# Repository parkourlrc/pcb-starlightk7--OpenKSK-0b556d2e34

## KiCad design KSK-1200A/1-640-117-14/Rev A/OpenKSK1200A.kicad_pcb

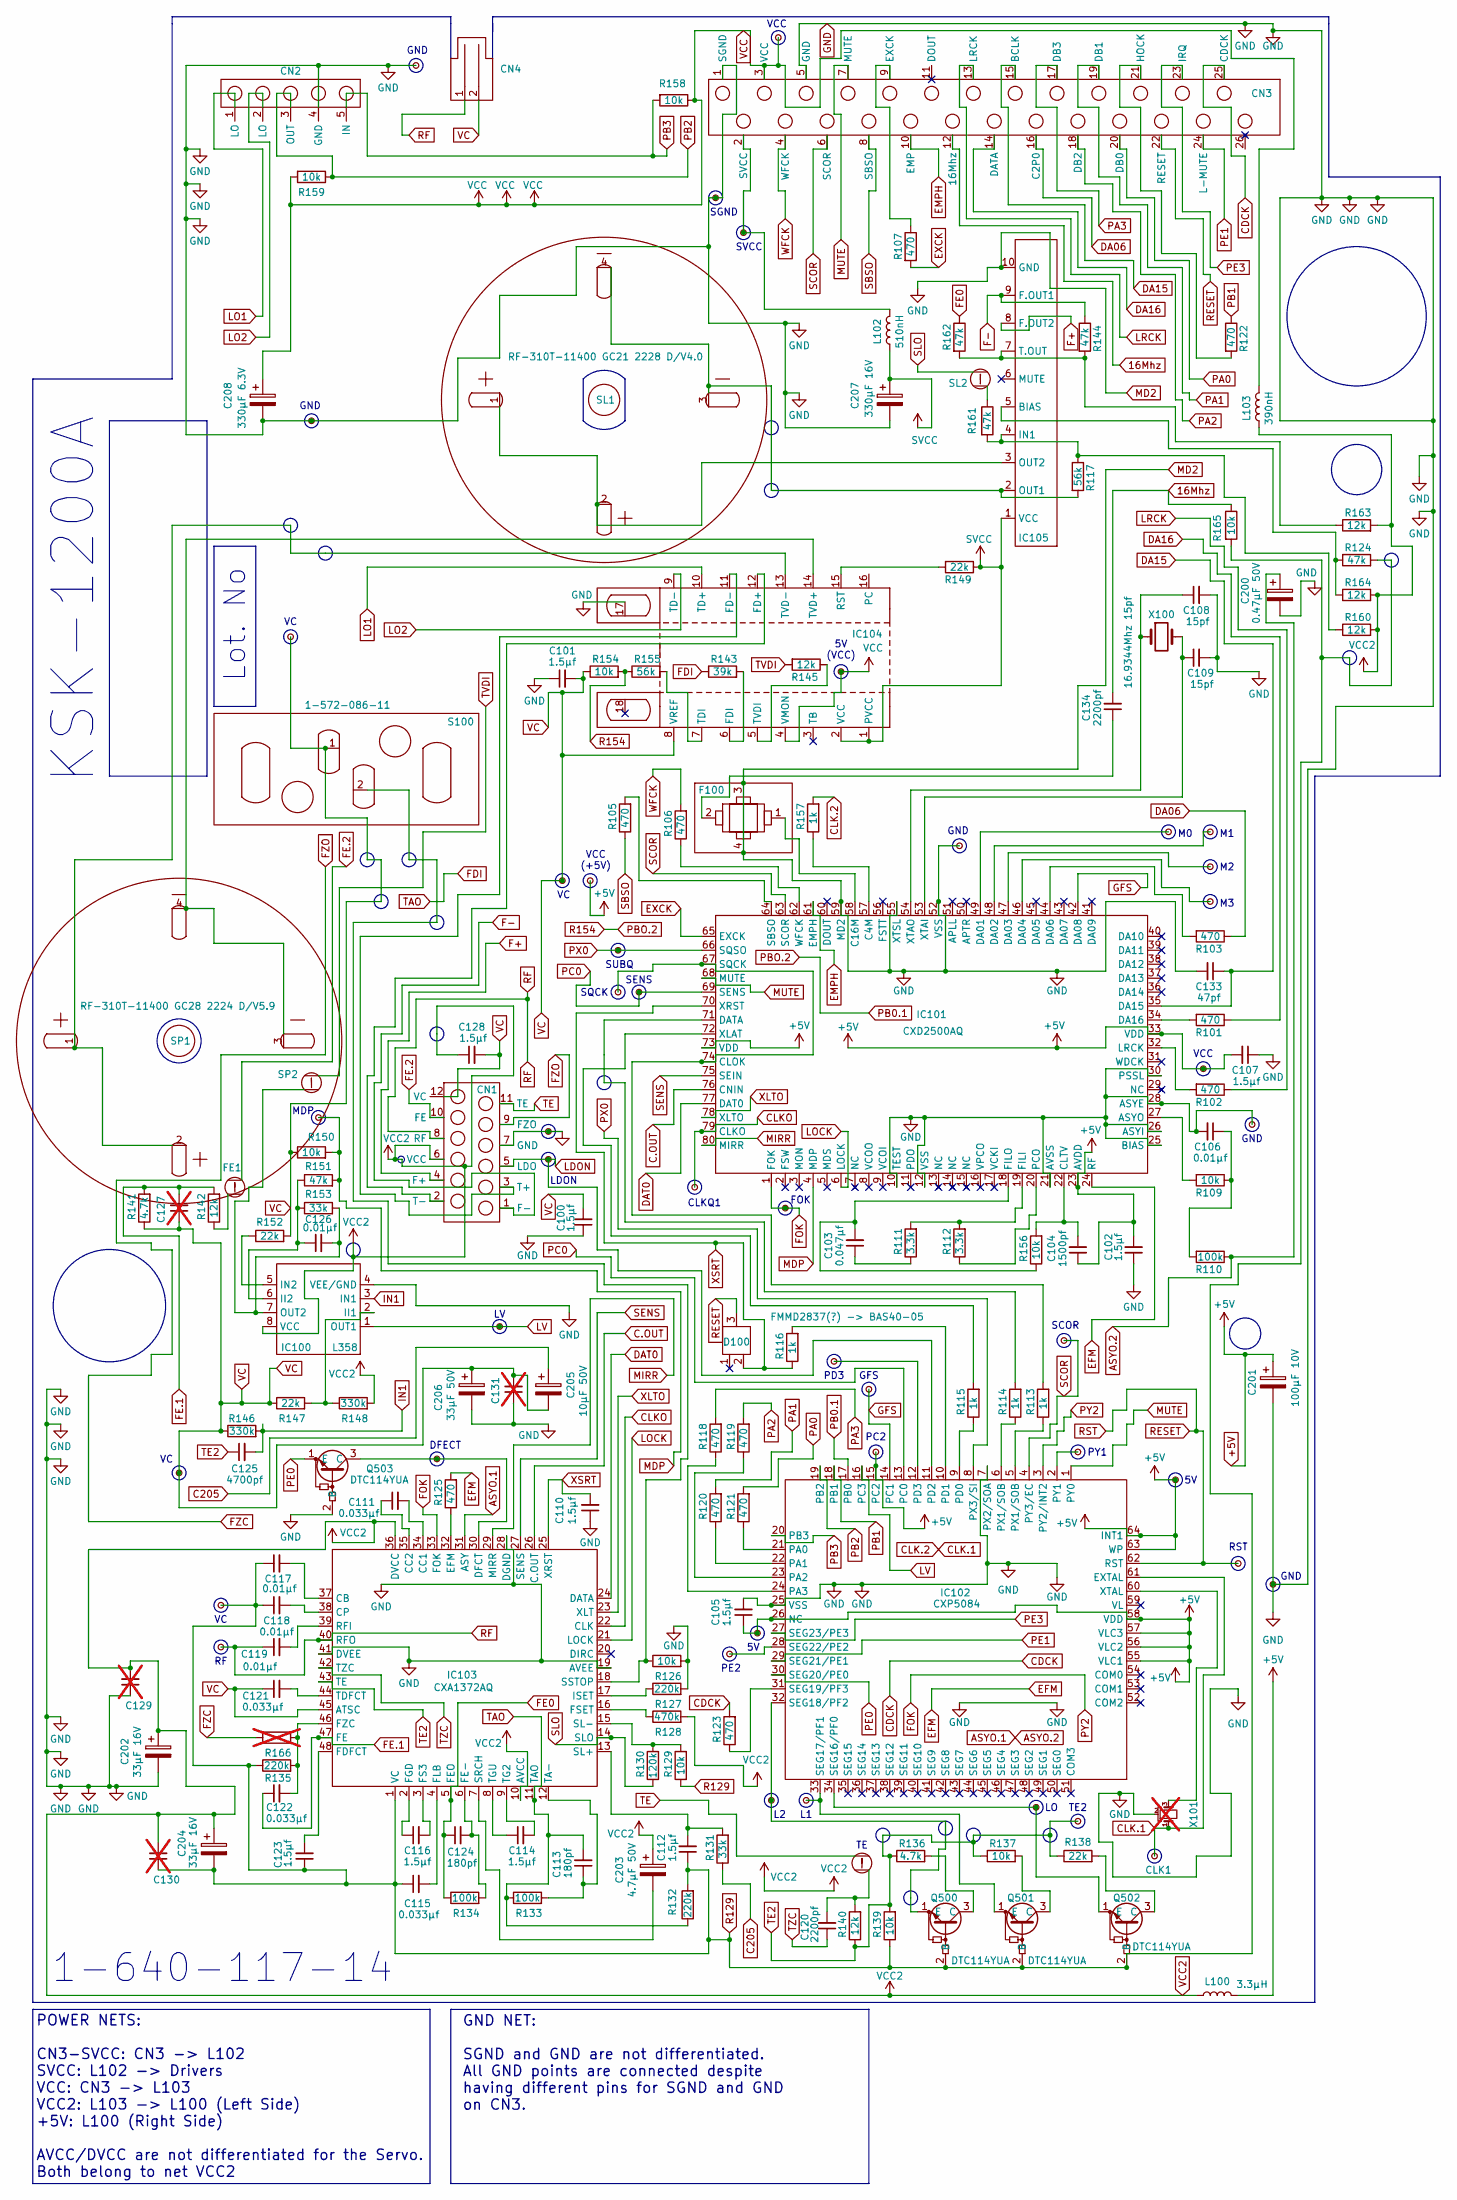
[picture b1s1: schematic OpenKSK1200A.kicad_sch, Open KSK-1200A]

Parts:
5V1, 5V2, 5V3: TestPoint_Small; TestPoint_Pad_D1.0mm
5V4: TestPoint_Small; TestPoint_Pad_D2.0mm
C100, C101, C102, C105, C107, C110, C112, C114, C116, C123, C128: 1.5µf; C_0805_2012Metric
C103: 0.047µf; C_0805_2012Metric
C104: 1500pf; C_0805_2012Metric
C106, C117, C118, C119, C126: 0.01µf; C_0805_2012Metric
C108, C109: 15pf; C_0805_2012Metric
C111, C115, C121, C122: 0.033µf; C_0805_2012Metric
C113, C124: 180pf; C_0805_2012Metric
C120, C134: 2200pf; C_0805_2012Metric
C125: 4700pf; C_0805_2012Metric
C127, C131: C_0805_2012Metric; not fitted
C129, C130: C_Small; C_0805_2012Metric; not fitted
C133: 47pf; C_0805_2012Metric
C200: 0.47µF 50V; THT Cap 0.5_0.5
C201: 100µF 10V; THT Cap 0.5_0.5
C202, C204: 33µF 16V; THT Cap 0.5_0.5
C203: 4.7µF 50V; THT Cap 0.5_0.5
C205: 10µF 50V; THT Cap 0.5_0.5
C206: 33µF 50V; THT Cap 0.5_0.5
C207: 330µF 16V; THT Cap 0.5_0.5
C208: 330µF 6.3V; THT Cap 0.5_0.5
CLK1: TestPoint_Small; TestPoint_Pad_D1.0mm
CLKQ1: TestPoint_Small; TestPoint_Pad_D1.0mm
CN1: CN1
CN2: CN2
CN3: CN3
CN4: CN4
D100: FMMD2837(?) -> BAS40-05; SOT-23_Handsoldering
DFECT1: TestPoint_Small; TestPoint_Pad_D1.0mm
F100: 350nH (L/R); F100
FE1: Jumper
FOK1: TestPoint_Small; TestPoint_Pad_D1.0mm
GFS1: TestPoint_Small; TestPoint_Pad_D2.0mm
GND1, GND2, GND4, GND5, GND6: TestPoint_Small; TestPoint_Pad_D2.0mm
GND3: TestPoint_Small; TestPoint_Pad_D1.0mm
IC100: L358; LM358
IC101: CXD2500AQ
IC102: CXP5084
IC103: CXA1372AQ; CXA1372Q
IC104: AN8377N
IC105: BA6294
L1, L2: TestPoint_Small; TestPoint_Pad_D1.0mm
L100: 3.3μH; L_1206_3216Metric
L102: 510nH; L_1806_4516Metric_Pad1.45x1.90mm_HandSolder
L103: 390nH; L_1206_3216Metric
LDON1: TestPoint_Small; TestPoint_Pad_D2.0mm
LO1: TestPoint_Small; TestPoint_Pad_D2.0mm
LV1: TestPoint_Small; TestPoint_Pad_D2.0mm
M0, M1, M2, M3: TestPoint_Small; TestPoint_Pad_D2.0mm
MDP1: TestPoint_Small; TestPoint_Pad_D2.0mm
PC2: TestPoint_Small; TestPoint_Pad_D1.0mm
PD3: TestPoint_Small; TestPoint_Pad_D2.0mm
PE2: TestPoint_Small; TestPoint_Pad_D2.0mm
PY1: TestPoint_Small; TestPoint_Pad_D2.0mm
Q500, Q501, Q502, Q503: DTC114YUA; SOT-323_SC-70
R101, R102, R103, R105, R106, R107, R118, R119, R120, R121, R122, R123, R125: 470; R_0805_2012Metric
R109, R126, R129, R137, R139, R150, R154, R156, R158, R159, R165: 10k; R_0805_2012Metric
R110, R133, R134: 100k; R_0805_2012Metric
R111, R112: 3.3k; R_0805_2012Metric
R113, R114, R115, R116, R157: 1k; R_0805_2012Metric
R117, R155: 56k; R_0805_2012Metric
R124, R144, R151, R161, R162: 47k; R_0805_2012Metric
R127, R132, R135: 220k; R_0805_2012Metric
R128: 470k; R_0805_2012Metric
R130: 120k; R_0805_2012Metric
R131, R153: 33k; R_0805_2012Metric
R136, R141: 4.7k; R_0805_2012Metric
R138, R147, R149, R152: 22k; R_0805_2012Metric
R140, R142, R145, R160, R163, R164: 12k; R_0805_2012Metric
R143: 39k; R_0805_2012Metric
R146, R148: 330k; R_0805_2012Metric
R166: R_0805_2012Metric; not fitted
RF1: TestPoint_Pad_D2.0mm
RST1: TestPoint_Small; TestPoint_Pad_D2.0mm
S100: 1-572-086-11; LimitSwitch
SCOR1: TestPoint_Small; TestPoint_Pad_D2.0mm
SENS1: TestPoint_Small; TestPoint_Pad_D1.0mm
SGND1: TestPoint_Small; TestPoint_Pad_D2.0mm
SL1: RF-310T-11400 GC21 2228 D/V4.0; SL1
SL2: Jumper
SP1: RF-310T-11400 GC28 2224 D/V5.9; SP1
SP2: Jumper
SQCK1: TestPoint_Small; TestPoint_Pad_D1.0mm
SUBG1: TestPoint_Small; TestPoint_Pad_D1.0mm
SVCC1: TestPoint_Small; TestPoint_Pad_D2.0mm
TE1: Jumper
TE2: TestPoint_Small; TestPoint_Pad_D2.0mm
VC1, VC2: TestPoint_Pad_D1.0mm
VC3, VC4: TestPoint_Small; TestPoint_Pad_D2.0mm
VCC2: TestPoint_Small; TestPoint_Pad_D2.0mm
VCC3: TestPoint_Small; TestPoint_Pad_D1.0mm
X100: 16.9344Mhz 15pf; Crystal_HC18-U_Vertical
X101: Crystal_HC49-U-3Pin_Vertical; not fitted

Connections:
16Mhz: C134.2, CN3.12 (16Mhz), R165.1
+5V: 5V1.1, 5V2.1, 5V4.1, C102.2, C104.1, C105.1, C107.2, C201.1, IC101.23 (AVDD), IC101.33 (VDD), IC101.73 (VDD), IC102.15 (PC2), IC102.26 (NC), IC102.55 (VLC1), IC102.56 (VLC2), IC102.57 (VLC3), IC102.58 (VDD), IC102.63 (WP), IC102.64 (INT1), L100.2, PC2.1, VCC3.1
ASYO.1: C200.1, IC103.31 (ASY), R110.1
C205: C205.1, R131.1
C.OUT: IC101.76 (CNIN), IC103.26 (C.OUT)
CDCK: CN3.25 (CDCK), R123.2
CLK.1: CLK1.1, IC102.61 (EXTAL), R157.2, X101.1
CLKO: CLKQ1.1, IC101.79 (CLKO), IC103.22 (CLK)
DA06: CN3.16 (C2P0), R103.1
DA15: C133.1, CN3.15 (BCLK), IC101.35 (DA15)
DA16: CN3.14 (DATA), R101.1
DAT0: IC101.77 (DAT0), IC103.24 (DATA)
EFM: IC101.24 (RF), R125.2
EMPH: CN3.10 (EMP), IC101.61 (EMPH)
EXCK: IC101.65 (EXCK), R107.2
F+: CN1.4 (F+), IC105.8 (F.OUT2)
F-: CN1.1 (F-), IC105.9 (F.OUT1), R144.1
FDI: C113.2, IC103.11 (TAO), R132.1, R133.1, R143.1
FE0: C124.1, IC103.5 (FEO), R134.1, R162.1
FE.1: C122.1, C127.2, IC103.47 (FE), R141.2, R142.2
FE.2: CN1.10 (FE), FE1.1
FOK: FOK1.1, IC101.1 (FOK), IC102.3 (PY2/INT2), IC103.33 (FOK)
FZC: CN1.9 (FZO), R166.1
GFS: GFS1.1, IC101.42 (DA08), IC102.14 (PC1)
GND: C100.1, C101.1, C102.1, C105.2, C106.2, C107.1, C108.2, C109.2, C110.1, C129.1, C131.1, C133.2, C200.2, C201.2, C202.2, C206.2, C207.2, C208.2, CN1.7 (GND), CN2.4 (GND), CN3.1 (SGND), CN3.5 (GND), F100.3, F100.4, GND1.1, GND2.1, GND3.1, GND4.1, GND5.1, GND6.1, IC100.4 (VEE/GND), IC101.10 (TEST), IC101.12 (VSS), IC101.21 (AVSS), IC101.25 (BIAS), IC101.26 (ASYI), IC101.28 (ASYE), IC101.30 (PSSL), IC101.52 (VSS), IC101.55 (XTSL), IC101.59 (MD2), IC102.7 (PX2/SOA), IC102.25 (VSS), IC103.19 (AVEE), IC103.28 (DGND), IC103.41 (DVEE), IC104.17, IC105.10 (GND), Q503.2 (B), R126.2, R127.2, SGND1.1, X101.2
IN1: C125.2, IC100.3 (IN1), R146.2
LDON: CN1.5 (LDO), IC102.11 (PD2), LDON1.1
LO1: CN2.1 (LO), IC104.10 (TD+)
LO2: CN2.2 (LO), IC104.9 (TD-)
LOCK: IC101.6 (LOCK), IC103.21 (LOCK)
LRCK: CN3.13 (LRCK), R102.1
LV: IC100.1 (OUT1), IC102.16 (PC3), LV1.1
MDP: IC101.4 (MDP), MDP1.1, R150.2, R151.2
MIRR: IC101.80 (MIRR), IC103.29 (MIRR)
MUTE: CN3.7 (MUTE), IC101.68 (MUTE), IC102.1 (PY0)
unnamed: C103.1, R111.1
unnamed: C106.1, R109.1, R110.2
unnamed: C120.2, R140.2, TE1.2
unnamed: C134.1, F100.2
unnamed: CN1.3 (T+), IC104.11 (FD-)
unnamed: CN1.2 (T-), IC104.12 (FD+)
unnamed: CN3.9 (EXCK), R107.1
unnamed: CN3.21 (HOCK), R122.2
unnamed: CN3.2 (SVCC), L102.2, SVCC1.1
unnamed: FE1.2, R142.1
unnamed: IC100.2 (II1), R147.2, R148.1
unnamed: C126.1, IC100.6 (II2), R151.1, R153.1
unnamed: IC100.5 (IN2), R152.1
unnamed: C126.2, IC100.7 (OUT2), R153.2, SP2.2
unnamed: IC101.27 (ASYO), R109.2
unnamed: IC101.57 (C4M), R157.1
unnamed: F100.1, IC101.58 (C16M)
unnamed: IC101.67 (SQCK), IC101.74 (CLOK), R113.2, SQCK1.1
unnamed: C104.2, IC101.22 (CLTV), R156.2
unnamed: IC101.49 (DA01), M0.1
unnamed: IC101.48 (DA02), M1.1
unnamed: IC101.47 (DA03), M2.1
unnamed: IC101.46 (DA04), M3.1
unnamed: IC101.44 (DA06), R103.2
unnamed: IC101.34 (DA16), R101.2
unnamed: IC101.71 (DATA), R114.2
unnamed: IC101.19 (FILI), R111.2, R112.2
unnamed: C103.2, IC101.18 (FILO), R156.1
unnamed: IC101.32 (LRCK), R102.2
unnamed: IC101.20 (PCO), R112.1
unnamed: IC101.64 (SBSO), R105.2
unnamed: IC101.62 (WFCK), R106.1
unnamed: IC101.72 (XLAT), R115.2
unnamed: C109.1, IC101.53 (XTAI), X100.2
unnamed: C108.1, IC101.54 (XTAO), X100.1
unnamed: IC102.21 (PA0), R121.1
unnamed: IC102.22 (PA1), R120.1
unnamed: IC102.23 (PA2), R119.1
unnamed: IC102.24 (PA3), R118.1
unnamed: IC102.9 (PD0), R115.1
unnamed: IC102.10 (PD1), R116.2
unnamed: IC102.12 (PD3), PD3.1
unnamed: IC102.5 (PX1/SOB), R113.1
unnamed: IC102.6 (PX1/SOB), R114.1
unnamed: IC102.2 (PY1), PY1.1
unnamed: IC102.34 (SEG16/PF0), LO1.1, Q502.1 (E)
unnamed: IC102.33 (SEG17/PF1), L1.1, Q501.1 (E)
unnamed: IC102.32 (SEG18/PF2), L2.1, Q500.1 (E)
unnamed: IC102.31 (SEG19/PF3), R123.1
unnamed: IC102.28 (SEG22/PE2), PE2.1
unnamed: IC102.60 (XTAL), X101.3
unnamed: C117.2, IC103.37 (CB)
unnamed: C111.2, IC103.34 (CC1)
unnamed: C111.1, IC103.35 (CC2)
unnamed: C118.2, IC103.38 (CP)
unnamed: DFECT1.1, IC103.30 (DFCT), Q503.3 (C)
unnamed: IC103.32 (EFM), R125.1
unnamed: C123.2, IC103.48 (FDFCT)
unnamed: C124.2, IC103.6 (FE-), R134.2
unnamed: C116.1, IC103.2 (FGD)
unnamed: C115.2, IC103.4 (FLB)
unnamed: C116.2, IC103.3 (FS3)
unnamed: IC103.16 (FSET), R128.1
unnamed: C122.2, IC103.46 (FZC), R135.2, R166.2
unnamed: IC103.17 (ISET), R127.1
unnamed: C119.2, IC103.39 (RFI)
unnamed: C112.2, IC103.13 (SL+), R131.2
unnamed: IC103.15 (SL-), R129.2, R130.2
unnamed: C203.2, IC103.7 (SRCH)
unnamed: IC103.18 (SSTOP), R126.1, S100.2
unnamed: C113.1, IC103.12 (TA-), R133.2
unnamed: C121.2, IC103.44 (TDFCT)
unnamed: C114.2, IC103.9 (TG2)
unnamed: C114.1, IC103.8 (TGU)
unnamed: IC104.6 (FDI), R143.2
unnamed: IC104.15 (RST), R149.2
unnamed: IC104.7 (TDI), R155.2
unnamed: IC104.14 (TVD+), SP1.3, SP1.4
unnamed: IC104.13 (TVD-), SP1.1, SP1.2
unnamed: IC104.5 (TVDI), R145.1
unnamed: IC105.5 (BIAS), R124.1, R164.1
unnamed: IC105.4 (IN1), R117.1, R160.1, R161.2
unnamed: IC105.2 (OUT1), R117.2, SL1.3, SL1.4
unnamed: IC105.3 (OUT2), SL1.1, SL1.2
unnamed: IC105.7 (T.OUT), R144.2, R162.2, R163.1
unnamed: Q500.3 (C), R136.2
unnamed: Q501.3 (C), R137.2
unnamed: Q502.3 (C), R138.2
unnamed: R161.1, SL2.2
PA0: CN3.20 (DB0), R121.2
PA1: CN3.19 (DB1), R120.2
PA2: CN3.18 (DB2), R119.2
PA3: CN3.17 (DB3), R118.2
PB0.1: IC102.17 (PB0), R154.2, R155.1
PB1: IC102.18 (PB1), R122.1
PB2: CN2.3 (OUT), IC102.19 (PB2), R159.1
PB3: CN2.5 (IN), IC102.20 (PB3), R158.2
PC0: IC101.69 (SENS), IC102.13 (PC0), SENS1.1
PE0: IC102.30 (SEG20/PE0), Q503.1 (E)
PE1: CN3.24 (L-MUTE), IC102.29 (SEG21/PE1)
PE3: CN3.23 (IRQ), IC102.27 (SEG23/PE3)
PX0: IC101.66 (SQSO), IC102.8 (PX3/SI), SUBG1.1
R129: C112.1, C115.1, C117.1, C118.1, C123.1, C130.1, C204.2, IC103.1 (VC), Q500.2 (B), Q501.2 (B), Q502.2 (B), R124.2, R129.1, R132.2, R135.1, R139.1, R165.2, VC2.1
RESET: CN3.22 (RESET), D100.3, IC102.62 (RST), RST1.1
RF: C119.1, CN1.8 (RF), CN4.1, IC103.40 (RFO), RF1.1
SBSO: CN3.8 (SBSO), R105.1
SCOR: CN3.6 (SCOR), IC101.63 (SCOR), IC102.4 (PY3/EC), SCOR1.1
SENS: IC101.75 (SEIN), IC103.27 (SENS)
SLO: IC103.14 (SLO), R130.1, SL2.1
SVCC: C207.1, IC104.1 (PVCC), IC104.2 (VCC), IC105.1 (VCC), L102.1, R149.1
TE: CN1.11 (TE), TE1.1
TE2: C125.1, IC103.43 (TE), R136.1, R137.1, R138.1, R139.2, R140.1, TE2.1
TVDI: R145.2, SP2.1
TZC: C120.1, IC103.42 (TZC)
VC: C100.2, C101.2, C121.1, C127.1, C128.2, C131.2, C205.2, C206.1, CN1.12 (VC), CN4.2, IC103.45 (ATSC), IC104.8 (VREF), R141.1, R146.1, R147.1, R150.1, R152.2, R154.1, S100.1, VC1.1, VC3.1, VC4.1
VCC: 5V3.1, C208.1, CN3.3 (VCC), IC104.4 (VMON), L103.2, R158.1, R159.2, VCC2.1
VCC2: C128.1, C129.2, C130.2, C202.1, C203.1, C204.1, CN1.6 (VCC), IC100.8 (VCC), IC103.10 (AVCC), IC103.36 (DVCC), L100.1, L103.1, R128.2, R148.2, R160.2, R163.2, R164.2
WFCK: CN3.4 (WFCK), R106.2
XLTO: IC101.78 (XLTO), IC103.23 (XLT)
XSRT: C110.2, D100.2, IC101.70 (XRST), IC103.25 (XRST), R116.1

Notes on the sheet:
1-640-117-14
VCC
SCOR
LDON
GND
PD3
SVCC
SENS
FOK
SQCK
GFS
SUBQ
TE2
SGND
GND NET: SGND and GND are not differentiated. All GND points are connected despite having different pins for SGND and GND on CN3.
CLKQ1
5V (VCC)
VCC (+5V)
POWER NETS: CN3-SVCC: CN3 -> L102 SVCC: L102 -> Drivers VCC: CN3 -> L103 VCC2: L103 -> L100 (Left Side) +5V: L100 (Right Side) AVCC/DVCC are not differentiated for the Servo. Both belong to net VCC2
Lot. No
PC2
RST
PE2
DFECT
MDP
KSK-1200A
PY1

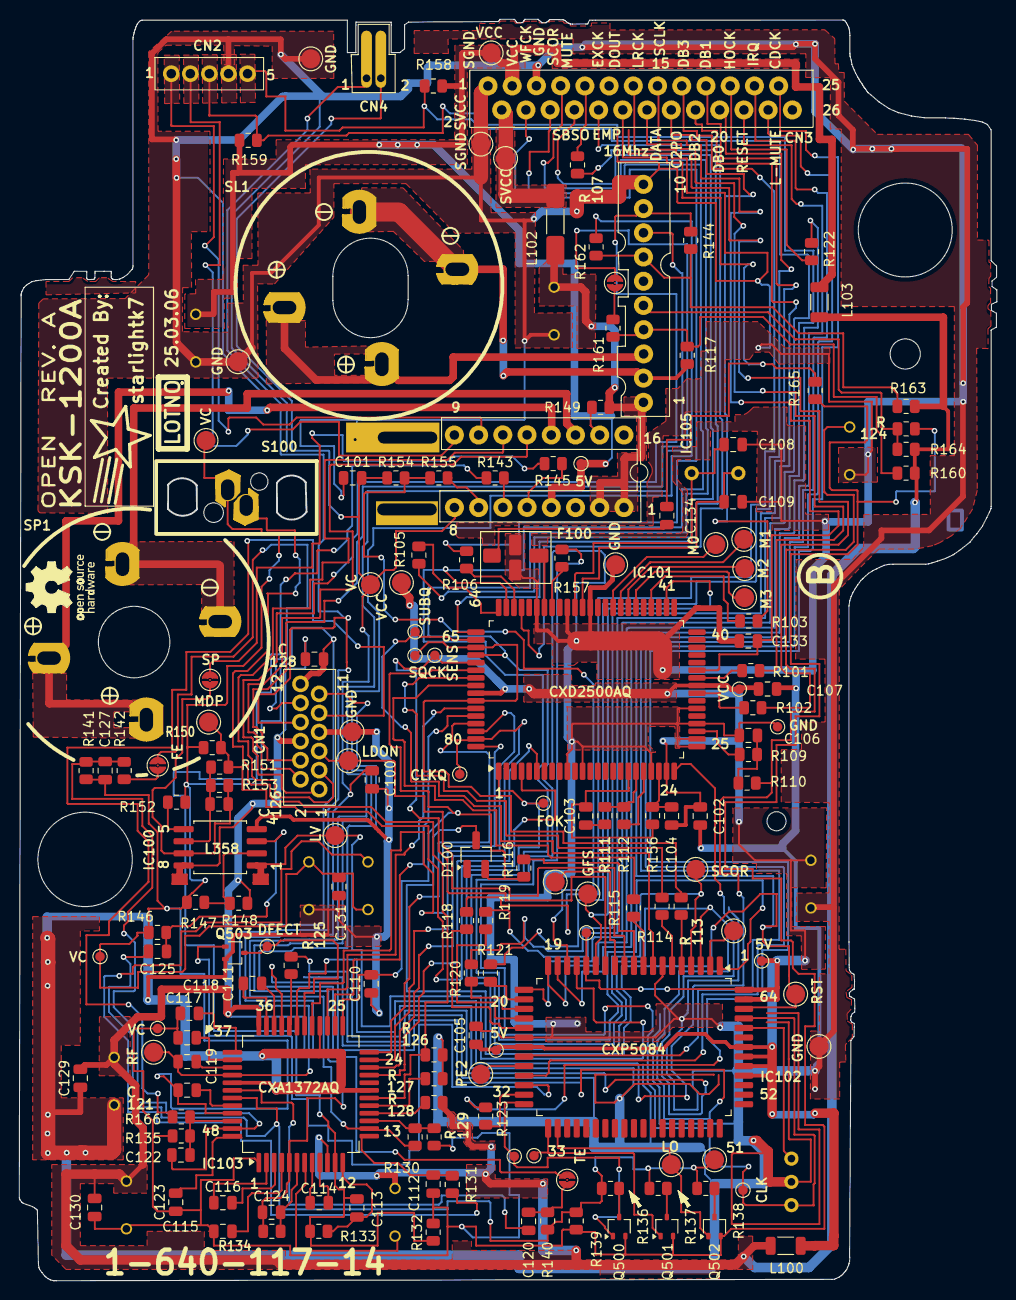
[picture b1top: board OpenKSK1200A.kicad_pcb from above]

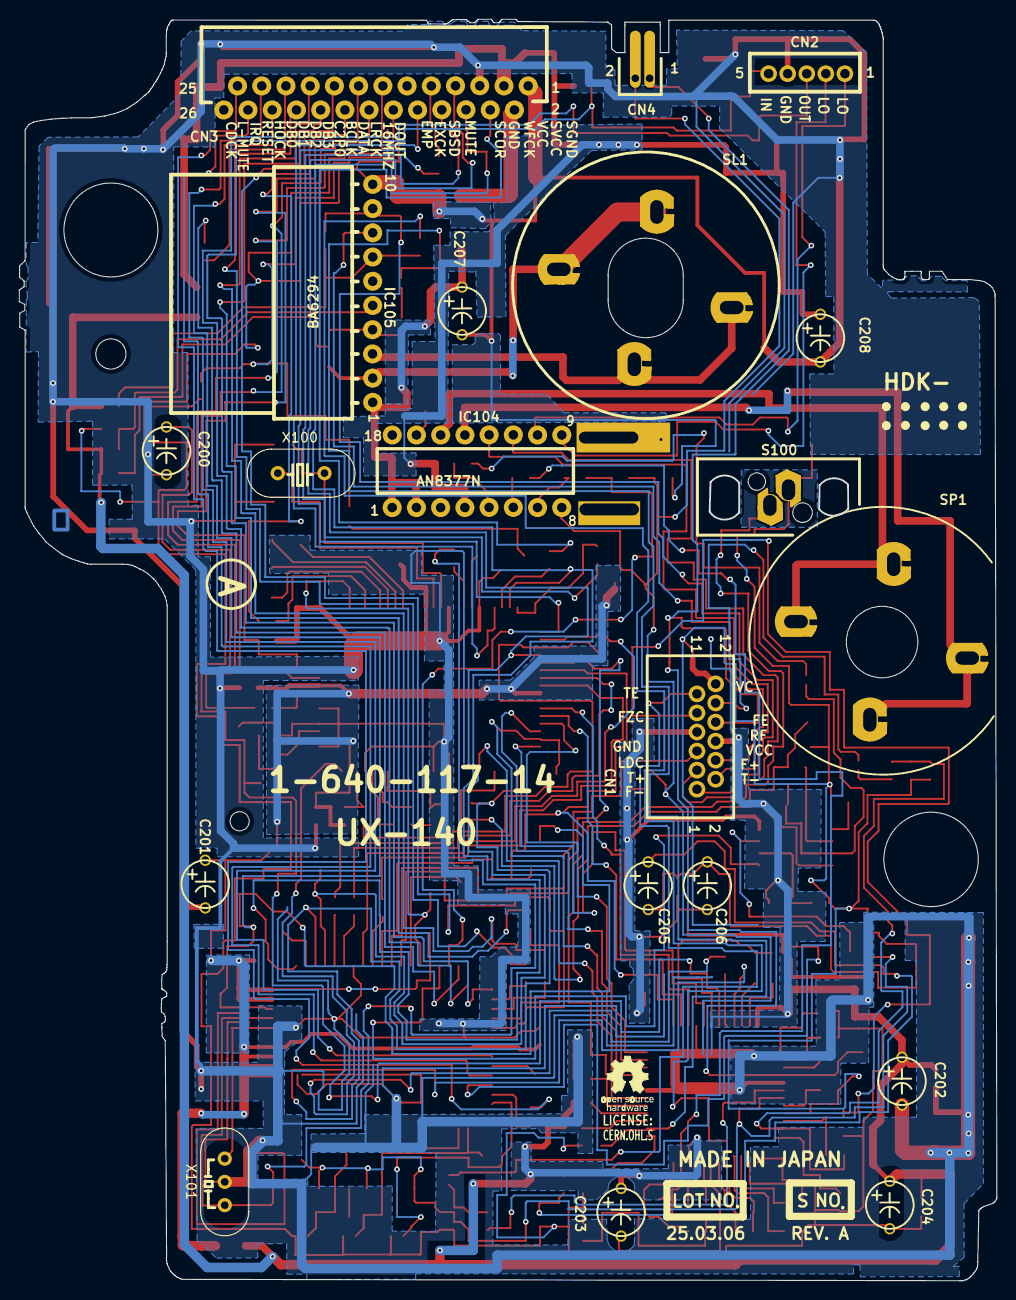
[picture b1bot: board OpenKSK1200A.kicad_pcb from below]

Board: 2 copper layers, 102.4 x 132.1 mm, 179 parts (14 on the bottom side), 155 nets.

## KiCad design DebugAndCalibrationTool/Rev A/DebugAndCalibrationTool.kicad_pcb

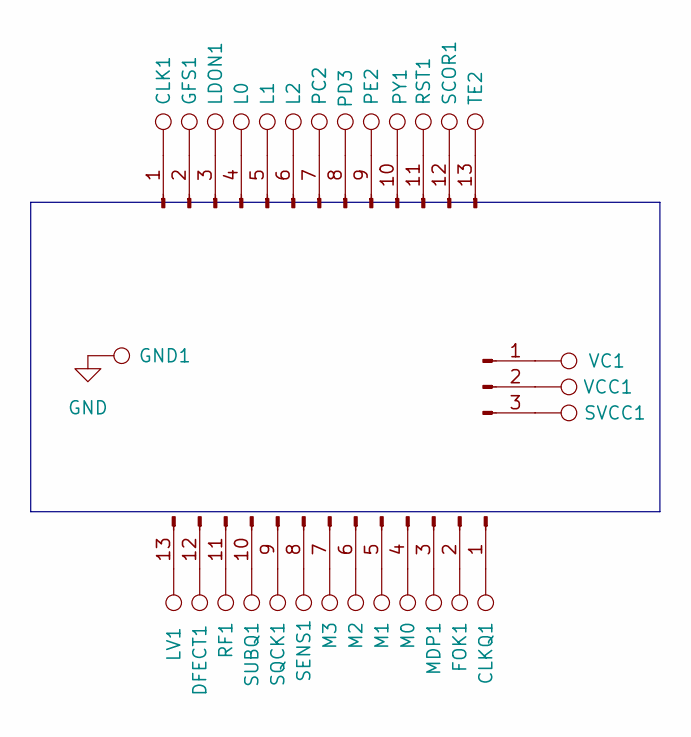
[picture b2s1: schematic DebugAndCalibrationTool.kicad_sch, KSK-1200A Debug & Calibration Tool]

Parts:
CLK1: TestPoint; TestPoint_Pad_D2.0mm
CLKQ1: TestPoint; TestPoint_Pad_D2.0mm
DFECT1: TestPoint; TestPoint_Pad_D2.0mm
FOK1: TestPoint; TestPoint_Pad_D2.0mm
GFS1: TestPoint; TestPoint_Pad_D2.0mm
GND1: TestPoint; TestPoint_Pad_D2.0mm
J4: Conn_01x04_Pin; PinHeader_1x08_P2.54mm_Vertical
J5, J6: Conn_01x13_Pin; PinHeader_1x26_P2.54mm_Vertical
L0, L1, L2: TestPoint; TestPoint_Pad_D2.0mm
LDON1: TestPoint; TestPoint_Pad_D2.0mm
LV1: TestPoint; TestPoint_Pad_D2.0mm
M0, M1, M2, M3: TestPoint; TestPoint_Pad_D2.0mm
MDP1: TestPoint; TestPoint_Pad_D2.0mm
PC2: TestPoint; TestPoint_Pad_D2.0mm
PD3: TestPoint; TestPoint_Pad_D2.0mm
PE2: TestPoint; TestPoint_Pad_D2.0mm
PY1: TestPoint; TestPoint_Pad_D2.0mm
RF1: TestPoint; TestPoint_Pad_D2.0mm
RST1: TestPoint; TestPoint_Pad_D2.0mm
SCOR1: TestPoint; TestPoint_Pad_D2.0mm
SENS1: TestPoint; TestPoint_Pad_D2.0mm
SQCK1: TestPoint; TestPoint_Pad_D2.0mm
SUBQ1: TestPoint; TestPoint_Pad_D2.0mm
SVCC1: TestPoint; TestPoint_Pad_D2.0mm
TE2: TestPoint; TestPoint_Pad_D2.0mm
VC1: TestPoint; TestPoint_Pad_D2.0mm
VCC1: TestPoint; TestPoint_Pad_D2.0mm

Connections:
GND: GND1.1
unnamed: J4.1, VC1.1
unnamed: J4.2, VCC1.1
unnamed: J4.3, SVCC1.1
unnamed: CLKQ1.1, J5.1
unnamed: FOK1.1, J5.2
unnamed: J5.3, MDP1.1
unnamed: J5.4, M0.1
unnamed: J5.5, M1.1
unnamed: J5.6, M2.1
unnamed: J5.7, M3.1
unnamed: J5.8, SENS1.1
unnamed: J5.9, SQCK1.1
unnamed: J5.10, SUBQ1.1
unnamed: J5.11, RF1.1
unnamed: DFECT1.1, J5.12
unnamed: J5.13, LV1.1
unnamed: CLK1.1, J6.1
unnamed: GFS1.1, J6.2
unnamed: J6.3, LDON1.1
unnamed: J6.4, L0.1
unnamed: J6.5, L1.1
unnamed: J6.6, L2.1
unnamed: J6.7, PC2.1
unnamed: J6.8, PD3.1
unnamed: J6.9, PE2.1
unnamed: J6.10, PY1.1
unnamed: J6.11, RST1.1
unnamed: J6.12, SCOR1.1
unnamed: J6.13, TE2.1

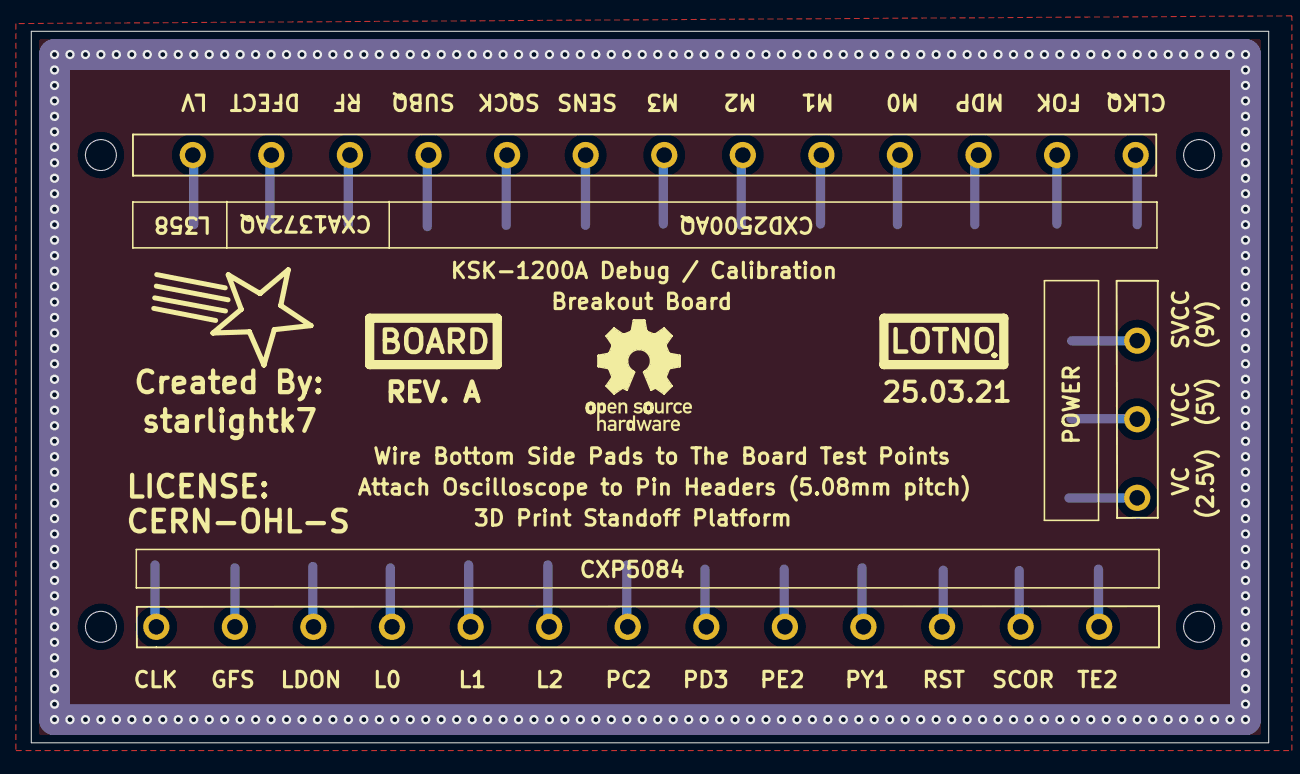
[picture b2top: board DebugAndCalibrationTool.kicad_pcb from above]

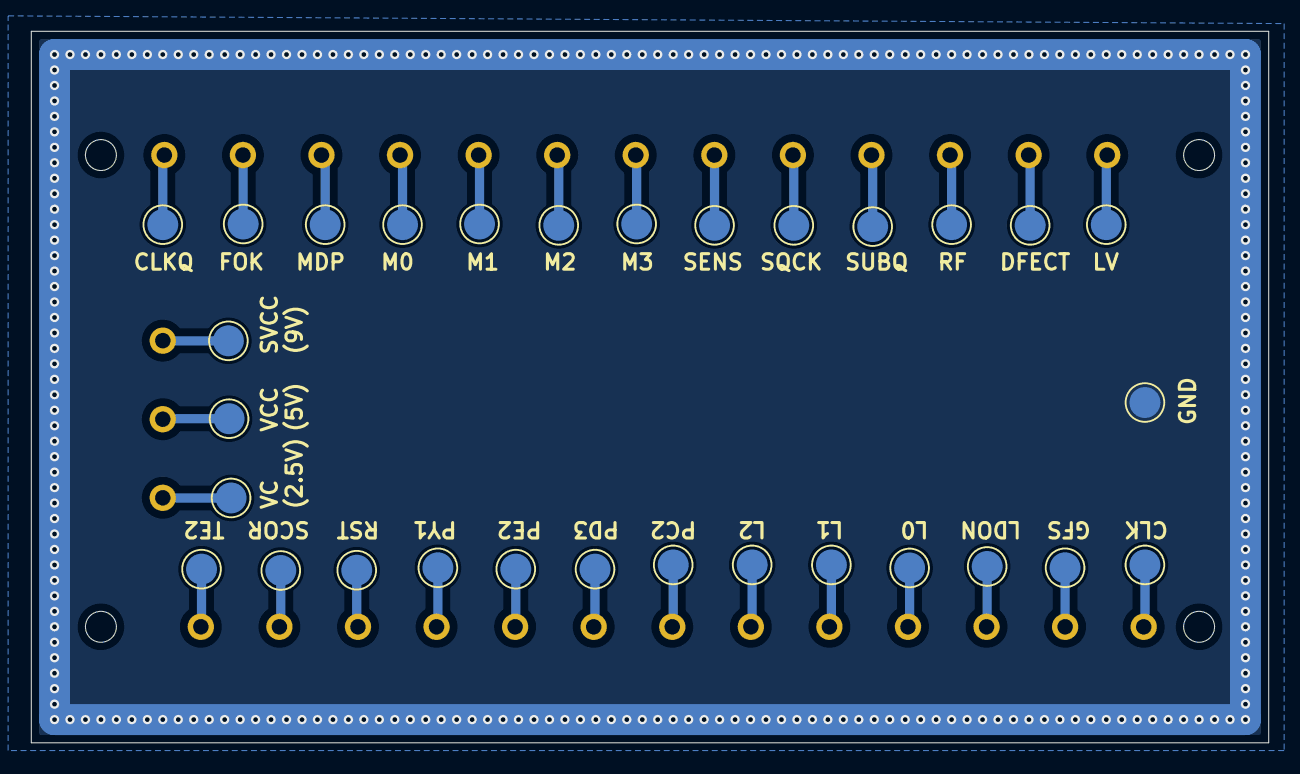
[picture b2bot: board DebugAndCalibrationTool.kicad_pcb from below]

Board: 2 copper layers, 80.0 x 46.0 mm, 33 parts (30 on the bottom side), 29 nets.

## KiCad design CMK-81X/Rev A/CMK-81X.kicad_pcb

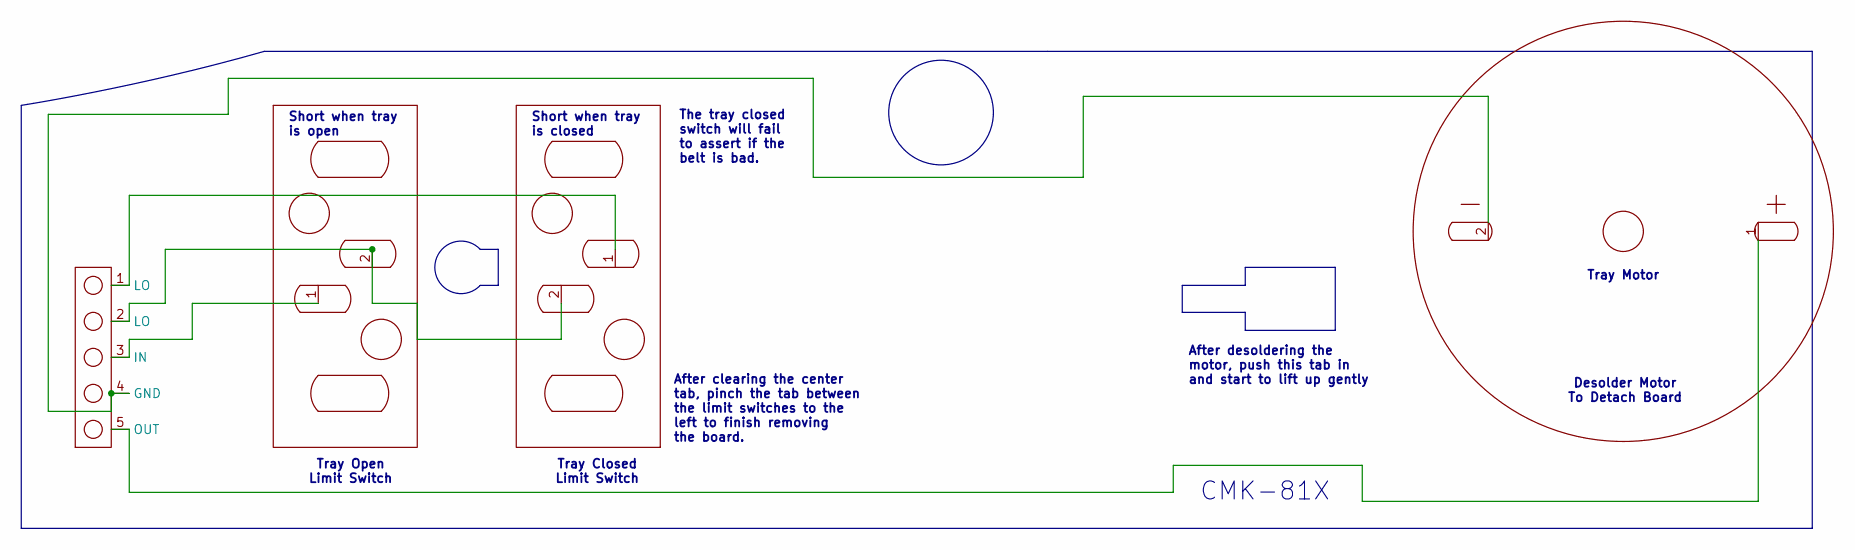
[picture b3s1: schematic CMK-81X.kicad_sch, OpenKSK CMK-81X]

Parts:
CN1: CN2
M1: Eject Motor
S1, S2: LimitSwitch

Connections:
unnamed: CN1.4 (GND), M1.2
unnamed: CN1.3 (IN), S1.1
unnamed: CN1.1 (LO), S2.1
unnamed: CN1.2 (LO), S1.2, S2.2
unnamed: CN1.5 (OUT), M1.1

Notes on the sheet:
Short when tray is closed
Tray Open Limit Switch
CMK-81X
Desolder Motor To Detach Board
The tray closed switch will fail to assert if the belt is bad.
Tray Motor
After desoldering the motor, push this tab in and start to lift up gently
Tray Closed Limit Switch
After clearing the center tab, pinch the tab between the limit switches to the left to finish removing the board.
Short when tray is open

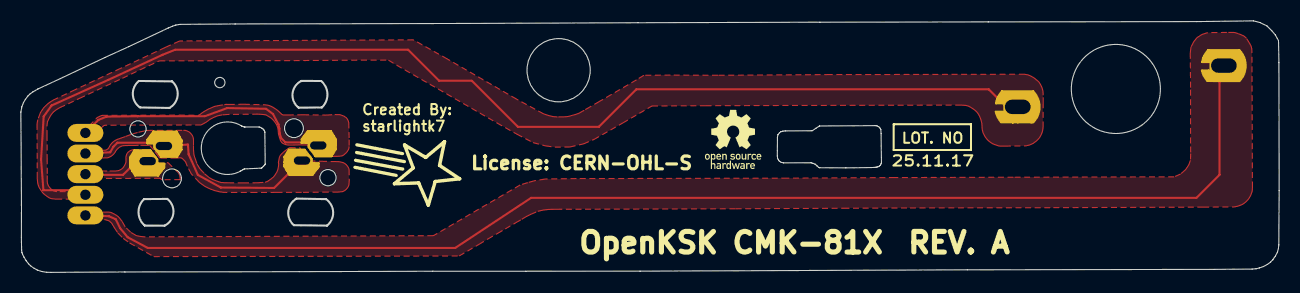
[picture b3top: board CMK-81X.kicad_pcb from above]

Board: 2 copper layers, 121.9 x 24.3 mm, 4 parts (0 on the bottom side), 5 nets.

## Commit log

2026-01-23 Initial Release
    First release of OpenKSK:
    OpenKSK-1200A 1-640-117-14
2026-01-24 First draft documentation

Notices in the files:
CMK-81X/Rev A/CMK-81X.kicad_pcb:
License: CERN-OHL-S
DebugAndCalibrationTool/Rev A/DebugAndCalibrationTool.kicad_pcb:
LICENSE:
CERN-OHL-S
